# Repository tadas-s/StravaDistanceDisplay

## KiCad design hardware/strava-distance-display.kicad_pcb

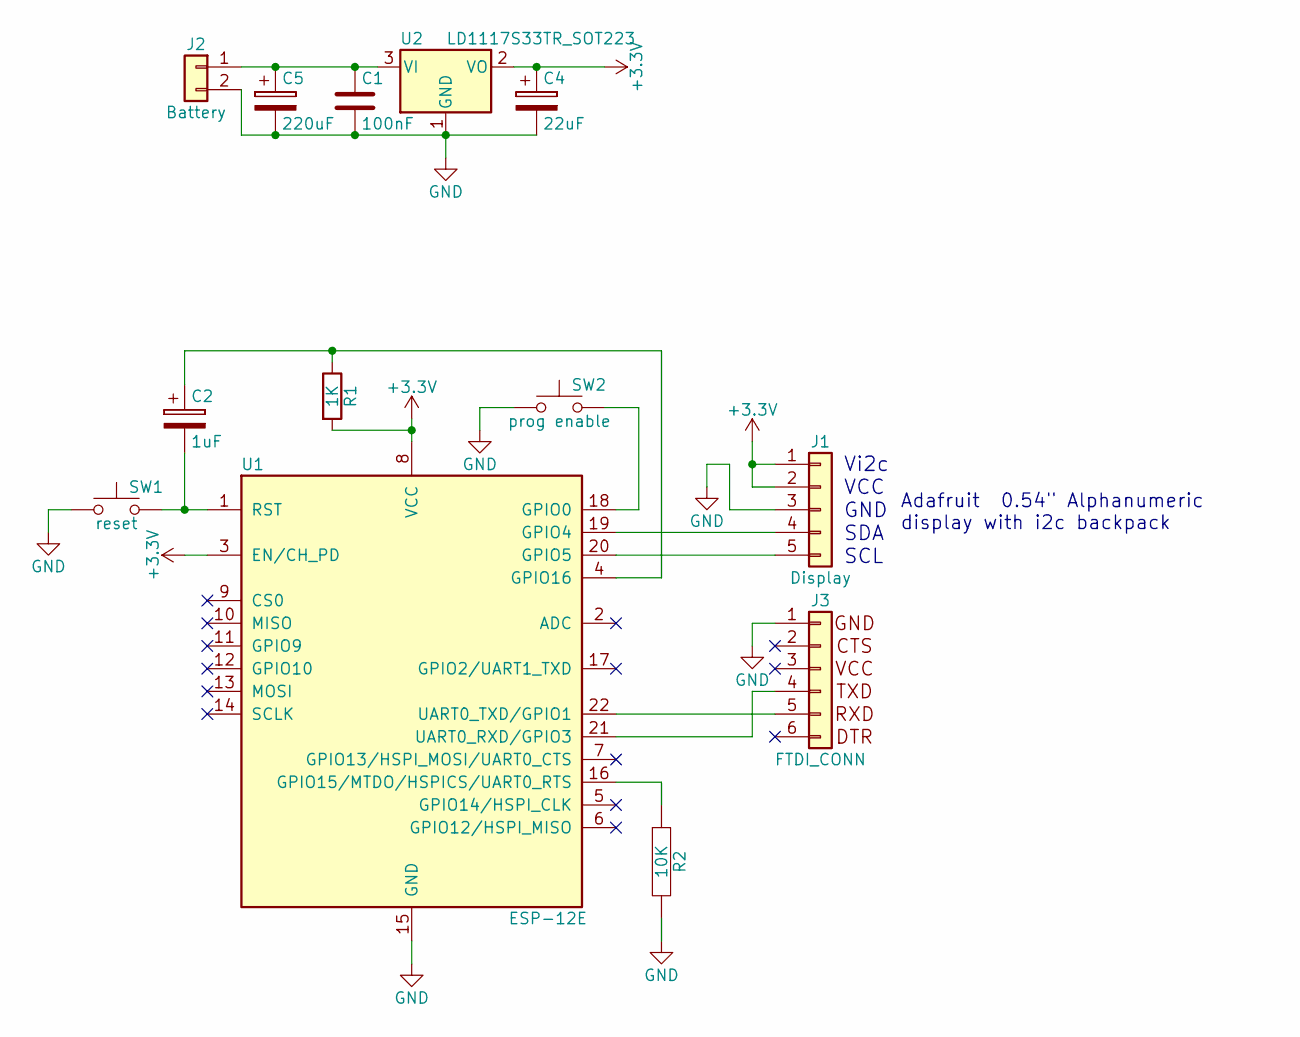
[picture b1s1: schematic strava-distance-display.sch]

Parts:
C1: 100nF; C_0805_HandSoldering
C2: 1uF; C_0805_HandSoldering
C4: 22uF; C_1206_HandSoldering
C5: 220uF; CP_Elec_6.3x5.8
J1: Display; Pin_Header_Straight_1x05_Pitch2.54mm
J2: Battery; Pin_Header_Angled_1x02_Pitch2.54mm
J3: FTDI_CONN; Pin_Header_Angled_1x06_Pitch2.54mm
R1: 1K; R_0805_HandSoldering
R2: 10K; R_0805_HandSoldering
SW1: reset; SW_Tactile_SKHH_Angled
SW2: prog enable; SW_Tactile_SKHH_Angled
U1: ESP-12E
U2: LD1117S33TR_SOT223; SOT-223

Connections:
+3V3: C4.1, J1.1, J1.2, R1.2, U1.3 (EN/CH_PD), U1.8 (VCC), U2.2 (VO)
GND: C1.2, C4.2, C5.2, J1.3, J2.2, J3.1, R2.2, SW1.1, SW2.1, U1.15 (GND), U2.1 (GND)
unnamed: C1.1, C5.1, J2.1, U2.3 (VI)
unnamed: C2.1, R1.1, U1.4 (GPIO16)
unnamed: C2.2, SW1.2, U1.1 (RST)
unnamed: J1.4, U1.19 (GPIO4)
unnamed: J1.5, U1.20 (GPIO5)
unnamed: J3.4, U1.21 (UART0_RXD/GPIO3)
unnamed: J3.5, U1.22 (UART0_TXD/GPIO1)
unnamed: R2.1, U1.16 (GPIO15/MTDO/HSPICS/UART0_RTS)
unnamed: SW2.2, U1.18 (GPIO0)

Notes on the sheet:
Vi2c VCC GND SDA SCL
Adafruit 0.54" Alphanumeric display with i2c backpack

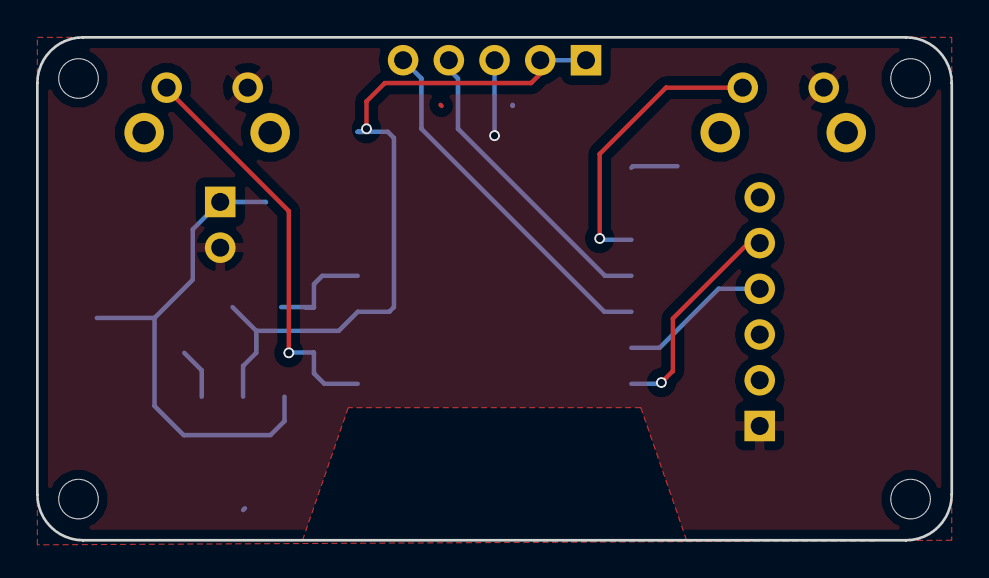
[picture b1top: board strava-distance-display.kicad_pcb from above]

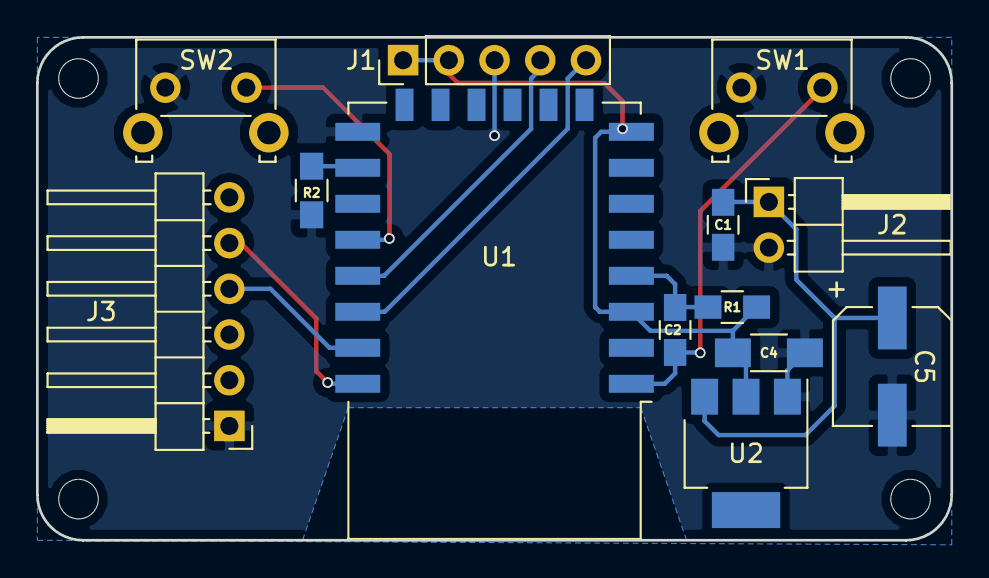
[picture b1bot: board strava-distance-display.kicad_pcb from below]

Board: 2 copper layers, 50.8 x 27.9 mm, 13 parts (13 on the bottom side), 11 nets.

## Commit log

2016-08-07 Rough initial sketch
2016-08-07 Configuration over serial, WIP
2016-08-08 Move display code to separate class
2016-08-08 Misc: some status messages via the main display
2016-08-09 Use TickerScheduler to schedule update and display tasks
2016-08-22 Simple scaffold to build / server AngularJS app, sample status json endpoint
2016-08-22 Serve Bootstrap as well + a very simple app to continuously refresh /status endpoint
2018-03-17 Update StravaDistanceDisplay.ino
    misc note about i2c bus pin assignments
2018-03-18 Schematic + pcb, WIP
2018-04-10 Schematic now uses built-in KiCad's ESP-12F symbol + footprint.
    And all the related error fixes as well..
2018-06-02 Hardware (#1)
    Schematic + PCB, verified!
